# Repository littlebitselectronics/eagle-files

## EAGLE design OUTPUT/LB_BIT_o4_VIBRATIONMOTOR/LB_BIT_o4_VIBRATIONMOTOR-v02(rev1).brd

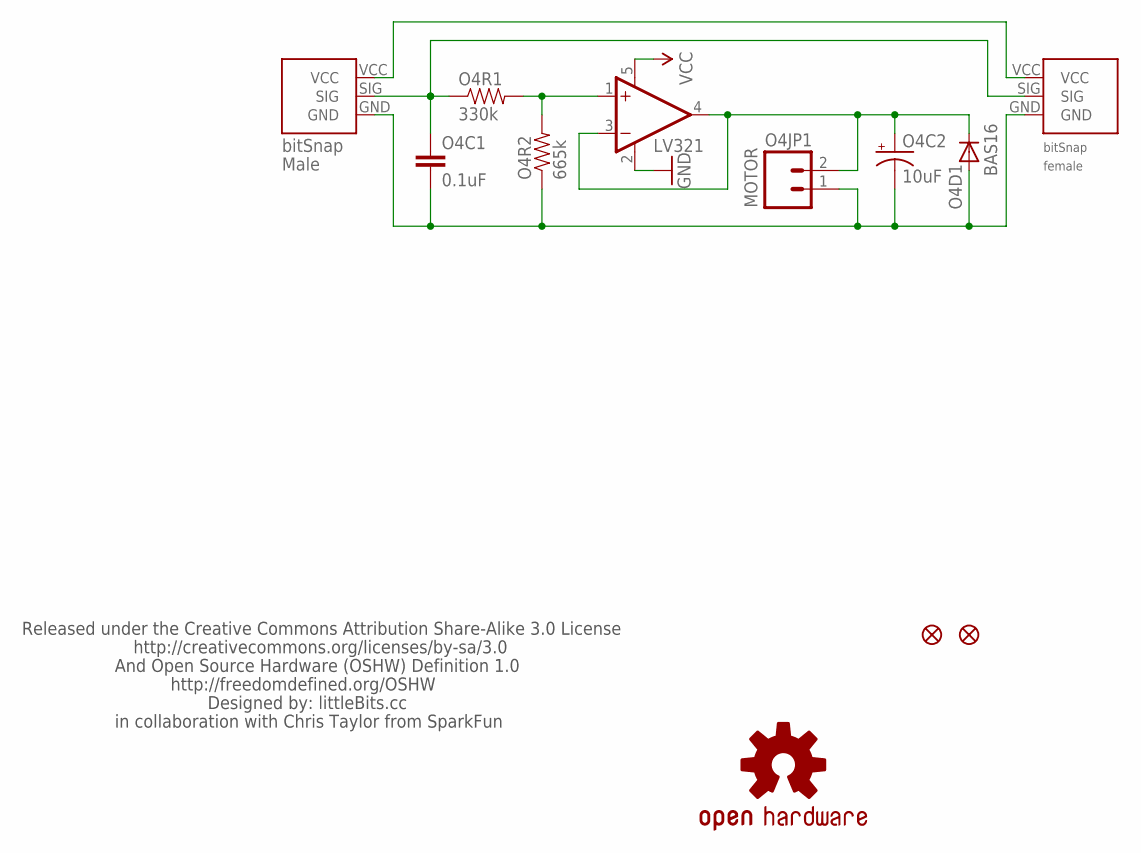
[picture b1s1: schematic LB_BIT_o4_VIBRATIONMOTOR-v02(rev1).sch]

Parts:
JP2, JP3: FIDUCIAL1X2.5; FIDUCIAL-1X2.5
O4BSF: BITSNAP_FEMALE
O4BSM: BITSNAP_MALE
O4C1: 0.1uF; 0603-CAP
O4C2: 10uF; EIA3216
O4D1: BAS16; SOT23-3
O4JP1: MOTOR; 1X02
O4R1: 330k; 0603-RES
O4R2: 665k; 0603-RES
O4U1: LV321; SC70
U$1: LB_CREDITS; OSHWCREDIT
U$5: OSHW-LOGOL; OSHW-LOGO-L

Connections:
GND: O4BSF.GND, O4BSM.GND, O4C1.2, O4C2.C (-), O4D1.1 (A), O4JP1.1, O4R2.1, O4U1.2 (V-)
unnamed: O4C2.A (+), O4D1.3 (C), O4JP1.2, O4U1.3 (-IN), O4U1.4 (OUT)
unnamed: O4R1.2, O4R2.2, O4U1.1 (+IN)
SIG: O4BSF.SIG, O4BSM.SIG, O4C1.1, O4R1.1
VCC: O4BSF.VCC, O4BSM.VCC, O4U1.5 (V+)

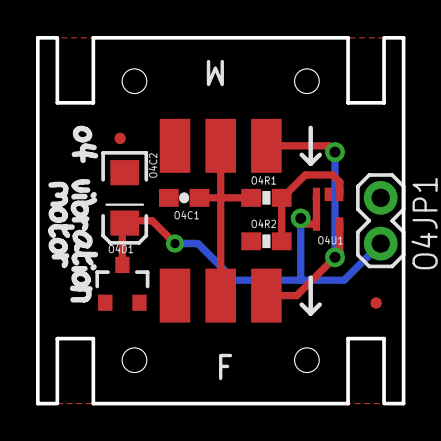
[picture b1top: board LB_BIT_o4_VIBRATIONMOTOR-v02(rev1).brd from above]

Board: 2 copper layers, 20.3 x 20.3 mm, 14 parts (0 on the bottom side), 5 nets.

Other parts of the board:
U$4: OSHW_FILLX150_NOTEXT

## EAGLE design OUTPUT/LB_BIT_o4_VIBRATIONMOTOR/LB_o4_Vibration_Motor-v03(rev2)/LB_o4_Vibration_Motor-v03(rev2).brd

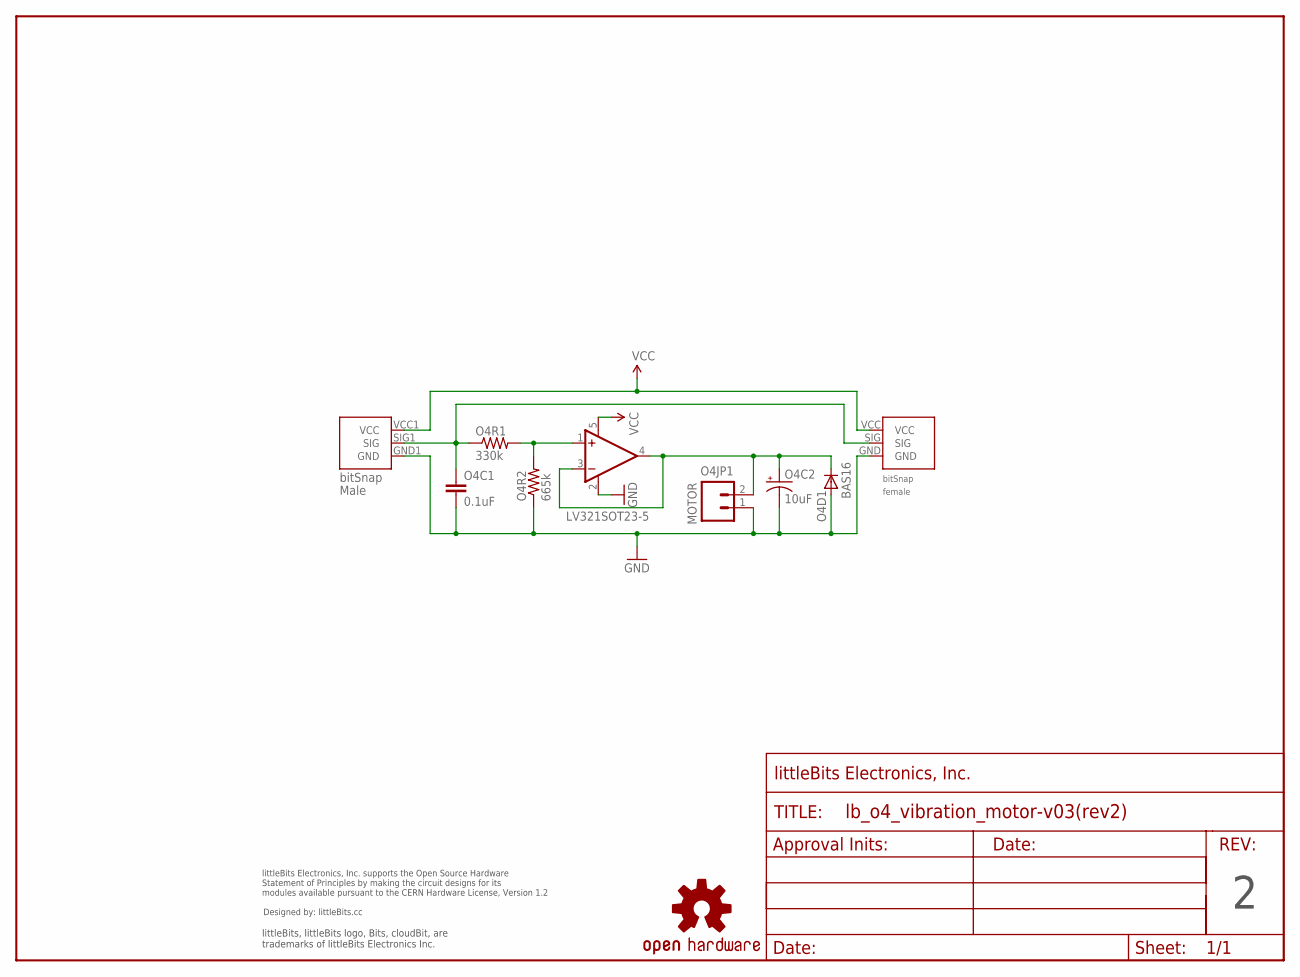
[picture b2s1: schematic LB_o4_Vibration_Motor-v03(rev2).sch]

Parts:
O4BSF1: BITSNAP_V03_FEMALE
O4BSM1: BITSNAP_V03_MALE
O4C1: 0.1uF; 0603-CAP
O4C2: 10uF; EIA3216
O4D1: BAS16; SOT23-3
O4JP1: MOTOR; JST-MICRO_2P
O4R1: 330k; 0603-RES
O4R2: 665k; 0603-RES
O4U1: LV321SOT23-5; SOT23-5
U$1: OSHWCREDIT
U$2: FRAME-LETTER-OHWOHW; FABDWG01-OHW
U$5: OSHW-LOGOL; OSHW-LOGO-L

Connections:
GND: O4BSF1.GND, O4BSM1.GND1 (GND), O4C1.2, O4C2.C (-), O4D1.1 (A), O4JP1.1, O4R2.1, O4U1.2 (V-)
unnamed: O4C2.A (+), O4D1.3 (C), O4JP1.2, O4U1.3 (-IN), O4U1.4 (OUT)
unnamed: O4R1.2, O4R2.2, O4U1.1 (+IN)
SIG: O4BSF1.SIG, O4BSM1.SIG1 (SIG), O4C1.1, O4R1.1
VCC: O4BSF1.VCC, O4BSM1.VCC1 (VCC), O4U1.5 (V+)

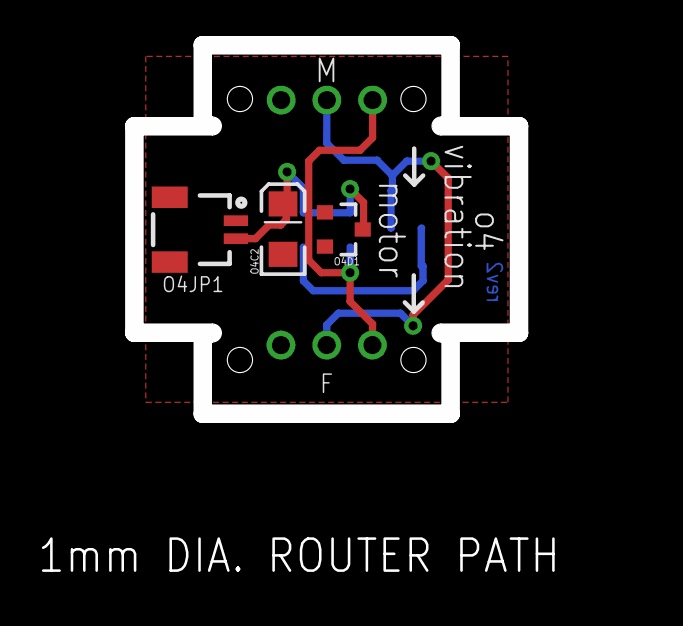
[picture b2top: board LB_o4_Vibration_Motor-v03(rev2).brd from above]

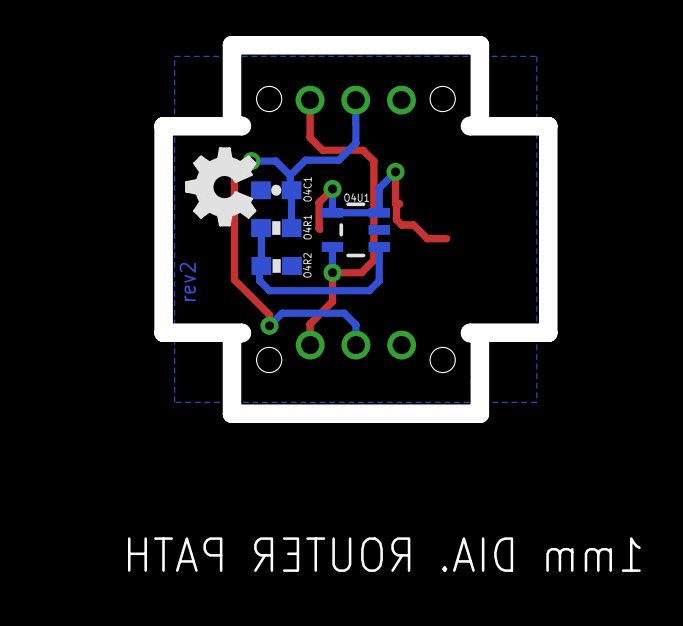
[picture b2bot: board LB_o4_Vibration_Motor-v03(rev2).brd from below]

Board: 2 copper layers, 21.4 x 20.5 mm, 13 parts (4 on the bottom side), 5 nets.

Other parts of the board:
U$4: OSHW_FILLX150_NOTEXT

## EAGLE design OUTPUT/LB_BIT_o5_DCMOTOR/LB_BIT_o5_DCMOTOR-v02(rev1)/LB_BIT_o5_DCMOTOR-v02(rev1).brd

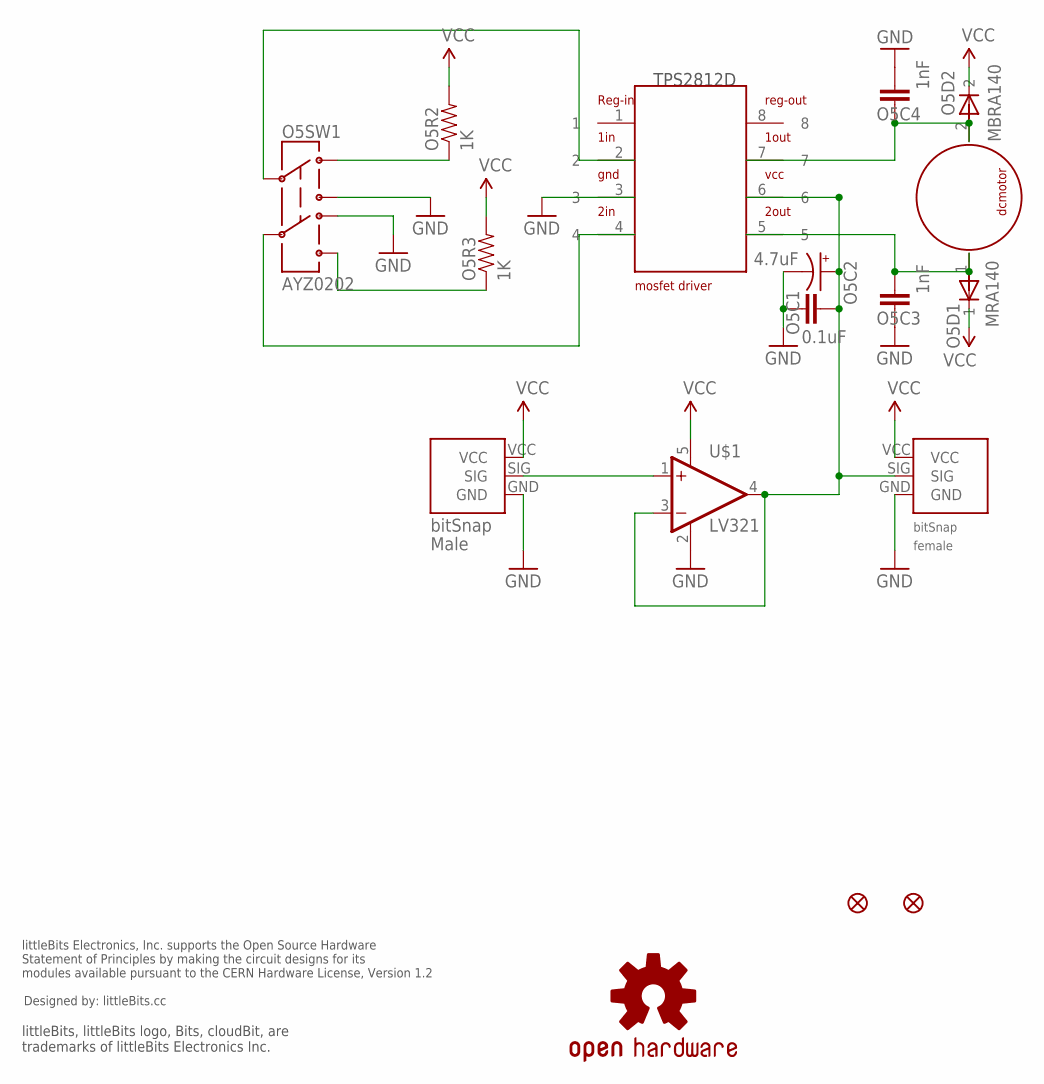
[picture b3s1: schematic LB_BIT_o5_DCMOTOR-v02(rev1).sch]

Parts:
JP1, JP2: FIDUCIAL1X2; FIDUCIAL-1X2
O5BSF: BITSNAP_FEMALE
O5BSM: BITSNAP_MALE
O5C1: 0.1uF; 0603-CAP
O5C2: 4.7uF; EIA3216
O5C3, O5C4: 1nF; 0603-CAP
O5D1: MRA140; SMA-DIODE
O5D2: MBRA140; SMA-DIODE
O5M1: DCMOTOR; MOTOR-DC
O5R2, O5R3: 1K; 0603-RES
O5SW1: AYZ0202
O5U1: TPS2812-SOIC8; TPS2812
U$1: LV321; SC70-5
U$4: OSHW-LOGOL; OSHW-LOGO-L
U$6: OSHWCREDIT

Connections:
GND: O5BSF.GND, O5BSM.GND, O5C1.1, O5C2.C (-), O5C3.1, O5C4.2, O5SW1.1 (3), O5SW1.6 (4), O5U1.3, U$1.2 (V-)
unnamed: O5BSM.SIG, U$1.1 (+IN)
unnamed: O5R2.1, O5SW1.3 (1)
unnamed: O5R3.1, O5SW1.4 (6)
unnamed: O5SW1.5, O5U1.4
unnamed: O5SW1.2, O5U1.2
unnamed: O5C4.1, O5D2.A, O5M1.2, O5U1.7
unnamed: O5C3.2, O5D1.A, O5M1.1, O5U1.5
SIG: O5BSF.SIG, O5C1.2, O5C2.A (+), O5U1.6, U$1.3 (-IN), U$1.4 (OUT)
VCC: O5BSF.VCC, O5BSM.VCC, O5D1.C, O5D2.C, O5R2.2, O5R3.2, U$1.5 (V+)

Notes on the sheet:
TPS2812D

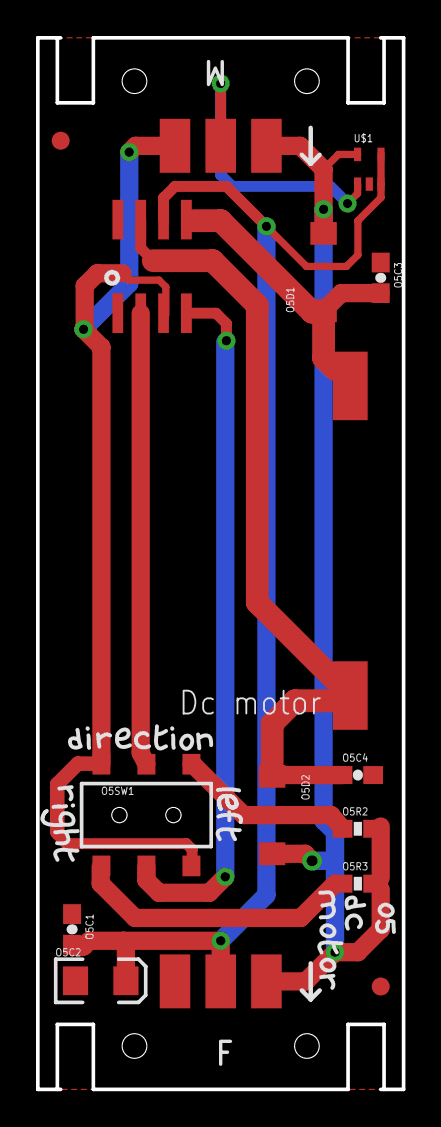
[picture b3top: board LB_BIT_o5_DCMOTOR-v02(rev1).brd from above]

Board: 2 copper layers, 20.3 x 58.4 mm, 47 parts (0 on the bottom side), 10 nets.

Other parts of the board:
U$2, U$38, U$40, U$49: O
U$3: 5
U$5, U$42: D
U$8: OSHW_FILLX150_NOTEXT
U$36, U$46: C
U$37: M
U$39, U$47, U$55, U$60: T
U$41, U$44, U$56: R
U$43, U$48, U$57: I
U$45, U$52, U$53: E
U$50: N
U$51: L
U$54: F
U$58: G
U$59: H

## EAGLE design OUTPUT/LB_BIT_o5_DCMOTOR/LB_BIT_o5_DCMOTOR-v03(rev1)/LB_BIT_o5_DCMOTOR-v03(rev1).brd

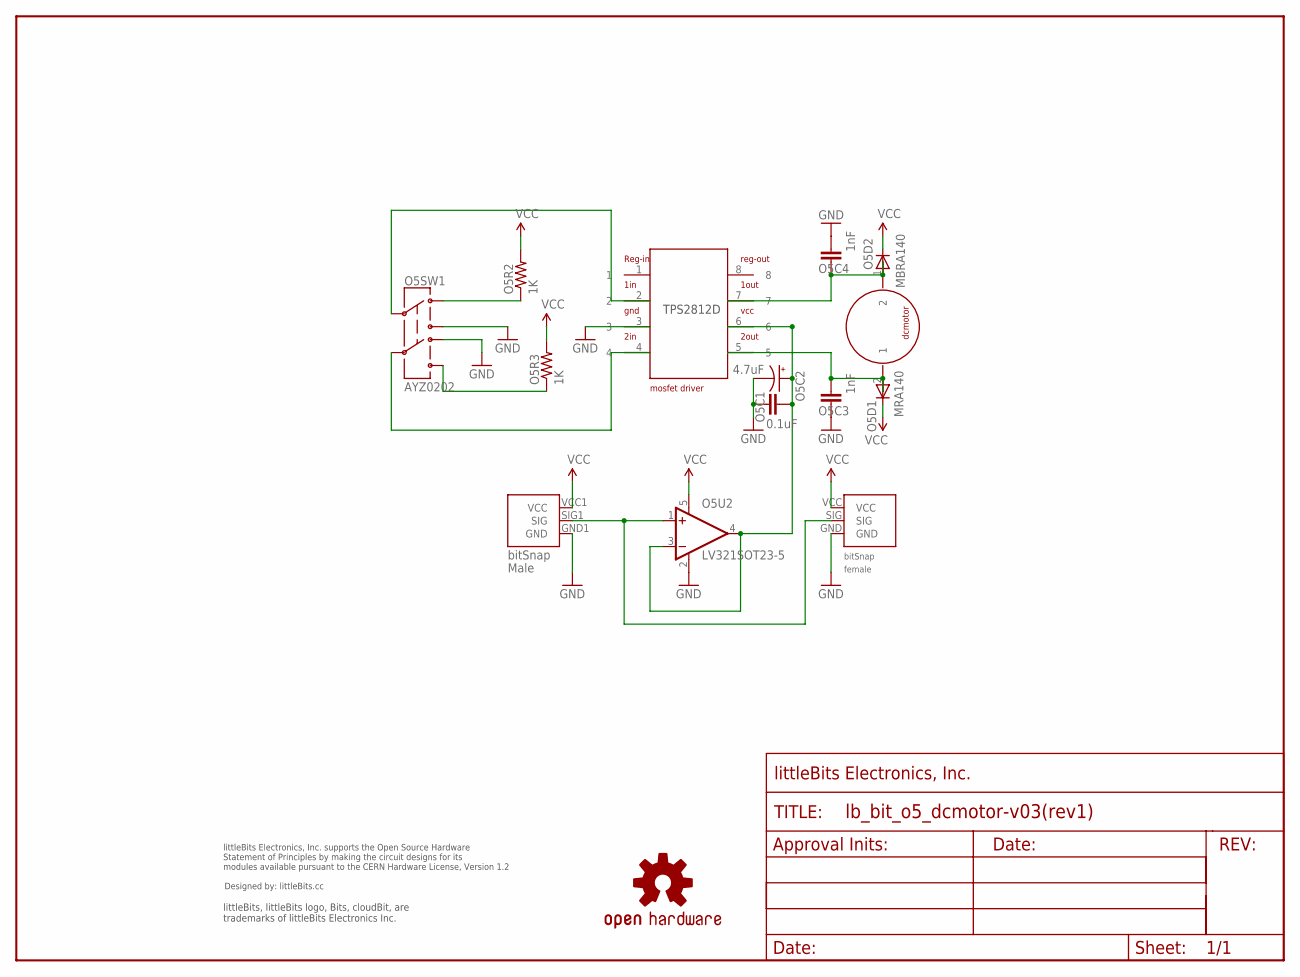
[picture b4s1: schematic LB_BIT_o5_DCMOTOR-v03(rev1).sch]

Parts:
O5BSF1: BITSNAP_V03_FEMALE
O5BSM1: BITSNAP_V03_MALE
O5C1: 0.1uF; 0603-CAP
O5C2: 4.7uF; EIA3216
O5C3, O5C4: 1nF; 0603-CAP
O5D1: MRA140; SMA-DIODE
O5D2: MBRA140; SMA-DIODE
O5M1: MOTOR-DC-GEARED; MOTOR-GEARED
O5R2, O5R3: 1K; 0603-RES
O5SW1: AYZ0202
O5U1: TPS2812-SOIC8; TPS2812
O5U2: LV321SOT23-5; SOT23-5
U$1: OSHWCREDIT
U$2: FRAME-LETTER-OHWOHW; FABDWG01-OHW
U$4: OSHW-LOGOL; OSHW-LOGO-L

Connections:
GND: O5BSF1.GND, O5BSM1.GND1 (GND), O5C1.1, O5C2.C (-), O5C3.1, O5C4.2, O5SW1.1 (3), O5SW1.6 (4), O5U1.3, O5U2.2 (V-)
unnamed: O5BSF1.SIG, O5BSM1.SIG1 (SIG), O5U2.1 (+IN)
unnamed: O5R2.1, O5SW1.3 (1)
unnamed: O5R3.1, O5SW1.4 (6)
unnamed: O5SW1.5, O5U1.4
unnamed: O5SW1.2, O5U1.2
unnamed: O5C4.1, O5D2.A, O5M1.1 (2), O5U1.7
unnamed: O5C3.2, O5D1.A, O5M1.2 (1), O5U1.5
SIG: O5C1.2, O5C2.A (+), O5U1.6, O5U2.3 (-IN), O5U2.4 (OUT)
VCC: O5BSF1.VCC, O5BSM1.VCC1 (VCC), O5D1.C, O5D2.C, O5R2.2, O5R3.2, O5U2.5 (V+)

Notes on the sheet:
TPS2812D

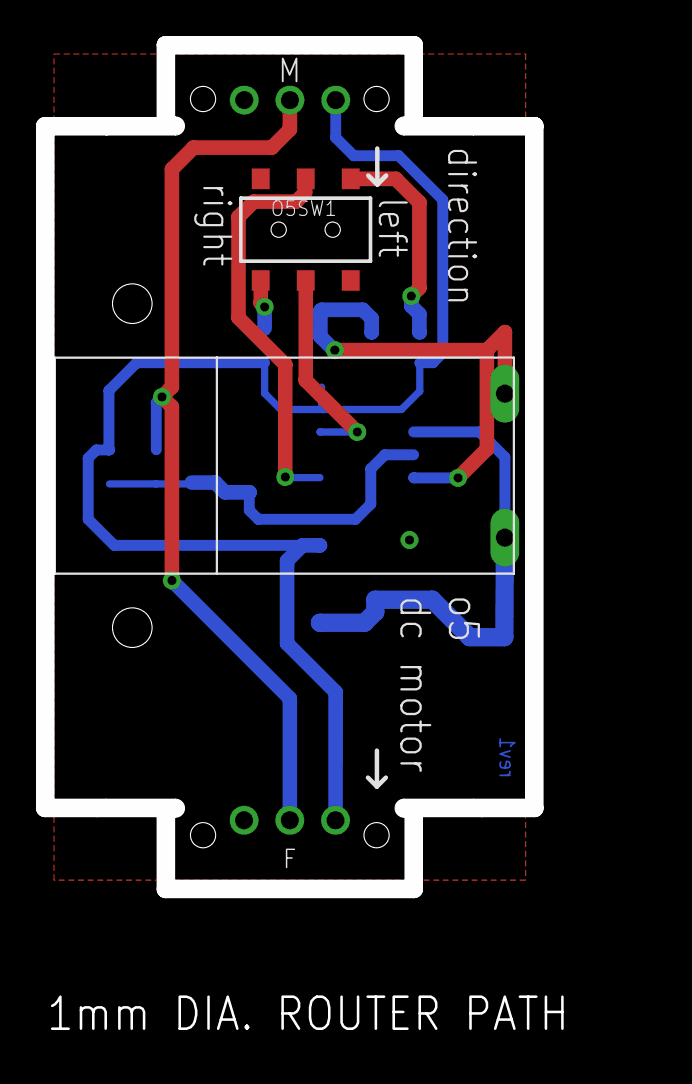
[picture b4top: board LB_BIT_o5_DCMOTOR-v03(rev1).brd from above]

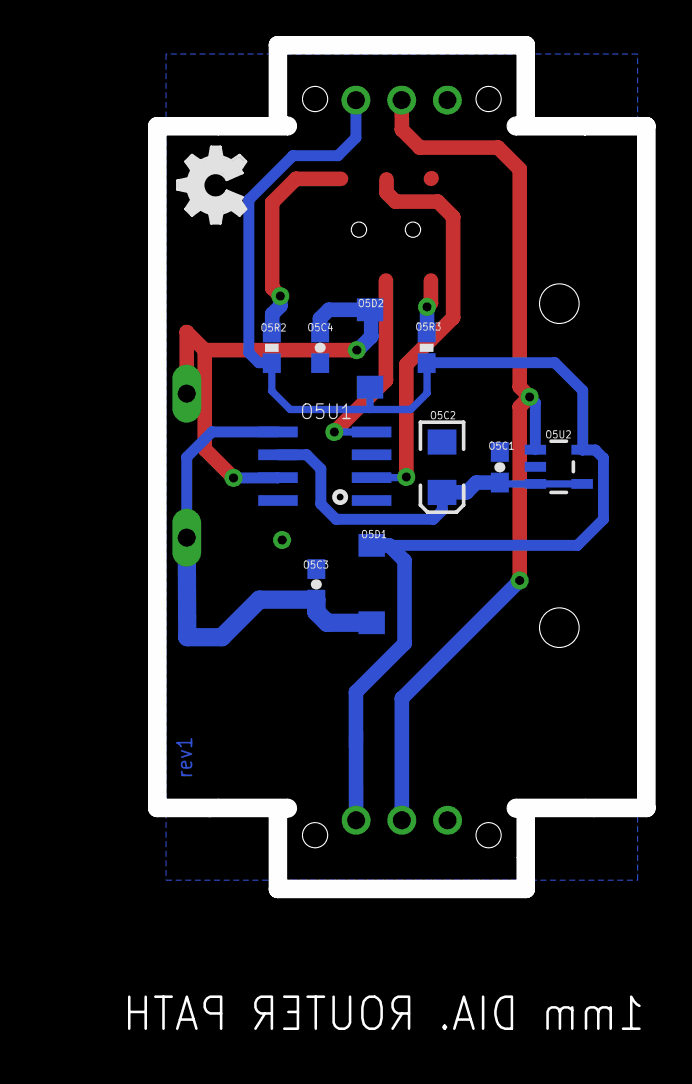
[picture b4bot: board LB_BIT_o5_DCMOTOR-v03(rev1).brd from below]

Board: 2 copper layers, 27.2 x 46.9 mm, 18 parts (10 on the bottom side), 10 nets.

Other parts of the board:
U$8: OSHW_FILLX150_NOTEXT

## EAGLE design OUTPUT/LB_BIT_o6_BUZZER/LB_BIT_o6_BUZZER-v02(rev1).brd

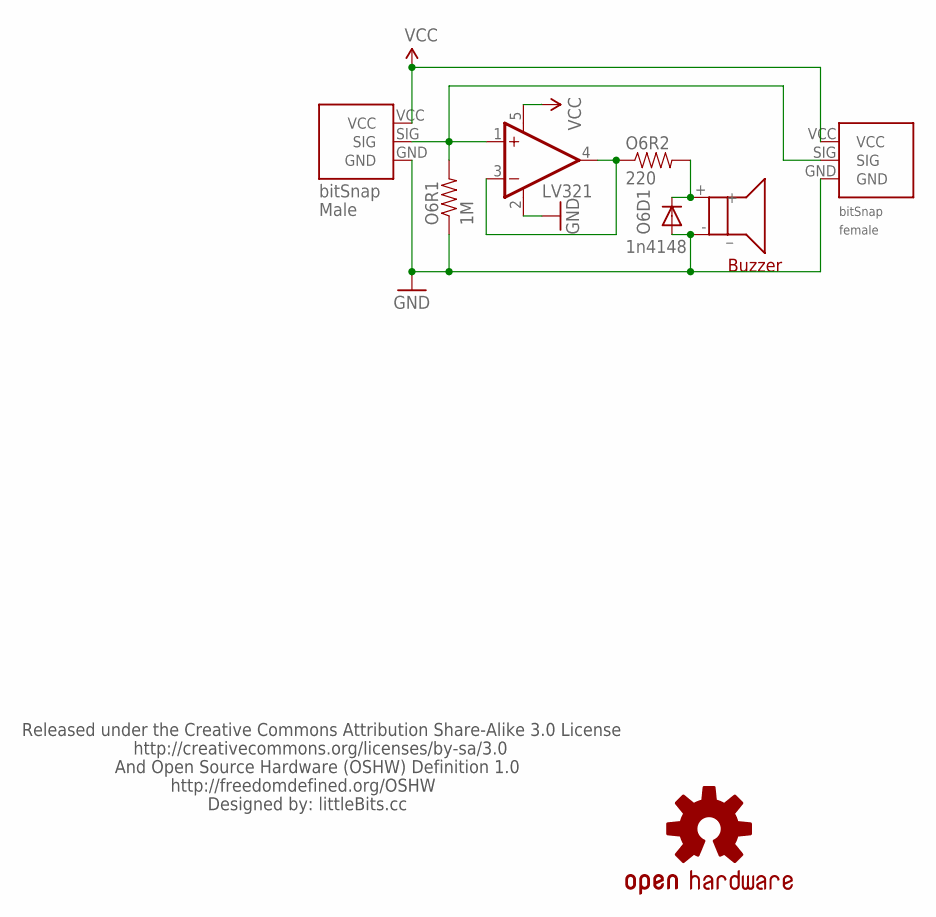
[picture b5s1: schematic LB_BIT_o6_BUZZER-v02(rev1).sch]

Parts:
O6BSF: BITSNAP_FEMALE
O6BSM: BITSNAP_MALE
O6D1: 1n4148; SOD-323
O6R1: 1M; 0603-RES
O6R2: 220; 0603-RES
O6U1: BUZZER-JSH2317AT
U$2: LV321; SC70
U$15: LB_CREDITS_V2
U$16: OSHW-LOGOL; OSHW-LOGO-L

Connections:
GND: O6BSF.GND, O6BSM.GND, O6D1.2 (A), O6R1.1, O6U1.- (_), U$2.2 (V-)
unnamed: O6D1.1 (C), O6R2.2, O6U1.+
unnamed: O6BSF.SIG, O6BSM.SIG, O6R1.2, U$2.1 (+IN)
unnamed: O6R2.1, U$2.3 (-IN), U$2.4 (OUT)
VCC: O6BSF.VCC, O6BSM.VCC, U$2.5 (V+)

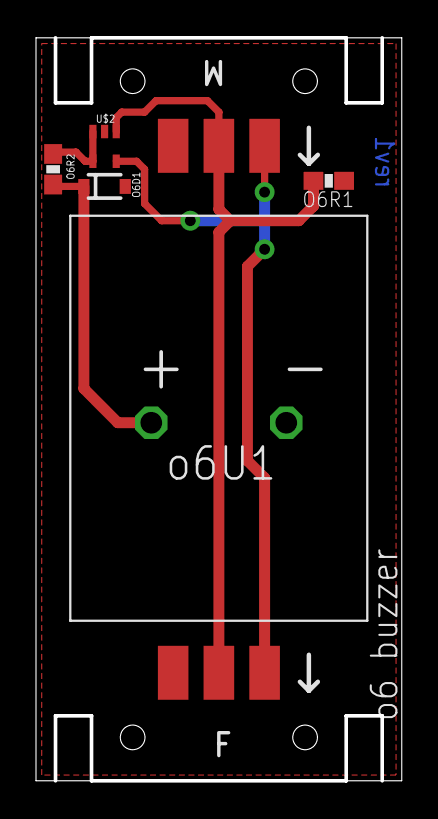
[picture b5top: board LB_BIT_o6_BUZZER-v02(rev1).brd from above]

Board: 2 copper layers, 20.3 x 41.3 mm, 10 parts (0 on the bottom side), 5 nets.

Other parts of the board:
U$7: OSHW_FILLX150_NOTEXT

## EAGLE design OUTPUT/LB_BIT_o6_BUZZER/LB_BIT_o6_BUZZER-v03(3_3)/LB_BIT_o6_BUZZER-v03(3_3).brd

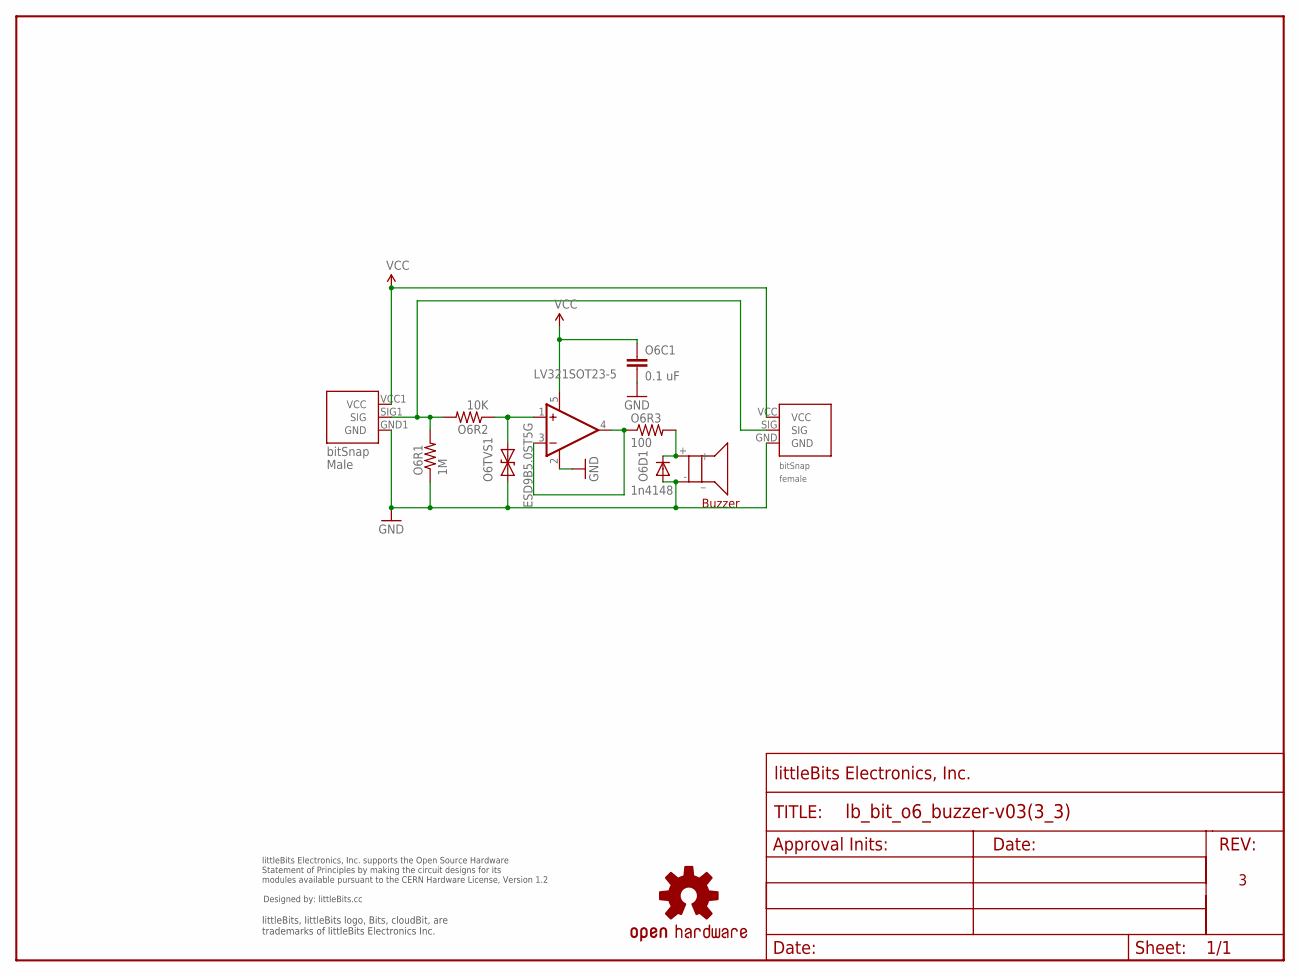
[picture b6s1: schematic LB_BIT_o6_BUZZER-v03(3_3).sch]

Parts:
O6BSF1: BITSNAP_V03_FEMALE
O6BSM1: BITSNAP_V03_MALE
O6C1: 0.1 uF; CAP-0603
O6D1: 1n4148; SOD-323
O6R1: 1M; RES-0603
O6R2: 10K; RES-0603
O6R3: 100; RES-0603
O6TVS1: ESD9B5.0ST5G; SOD-923
O6U1: LV321SOT23-5; SOT23-5
O6U2: BUZZER-JSH2317AT
U$1: FRAME-LETTER-OHWOHW; FABDWG01-OHW
U$2: OSHWCREDIT
U$16: OSHW-LOGOL; OSHW-LOGO-L

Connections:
GND: O6BSF1.GND, O6BSM1.GND1 (GND), O6C1.2, O6D1.2 (A), O6R1.1, O6TVS1.1 (A), O6U1.2 (V-), O6U2.- (_)
unnamed: O6D1.1 (C), O6R3.2, O6U2.+
unnamed: O6R2.1, O6TVS1.2 (C), O6U1.1 (+IN)
unnamed: O6BSF1.SIG, O6BSM1.SIG1 (SIG), O6R1.2, O6R2.2
unnamed: O6R3.1, O6U1.3 (-IN), O6U1.4 (OUT)
VCC: O6BSF1.VCC, O6BSM1.VCC1 (VCC), O6C1.1, O6U1.5 (V+)

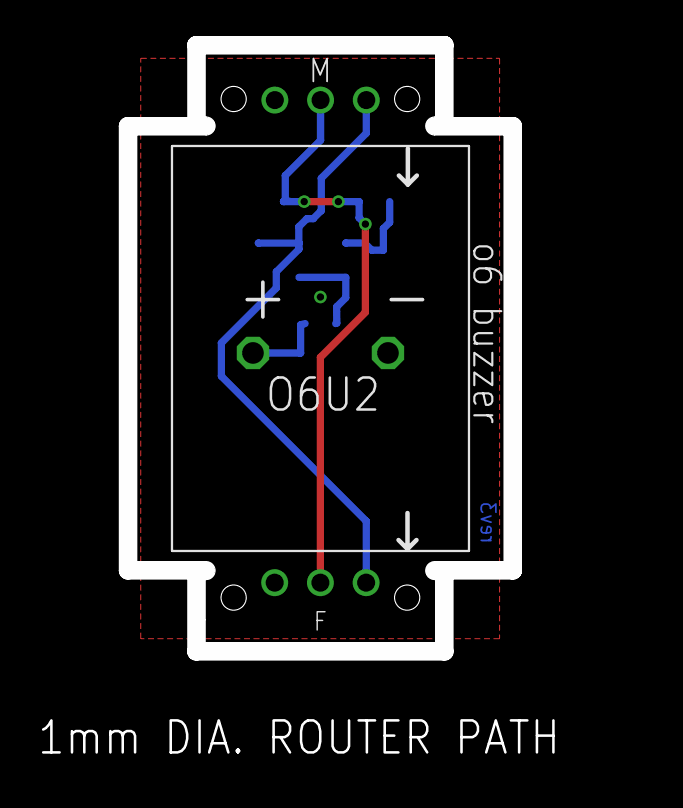
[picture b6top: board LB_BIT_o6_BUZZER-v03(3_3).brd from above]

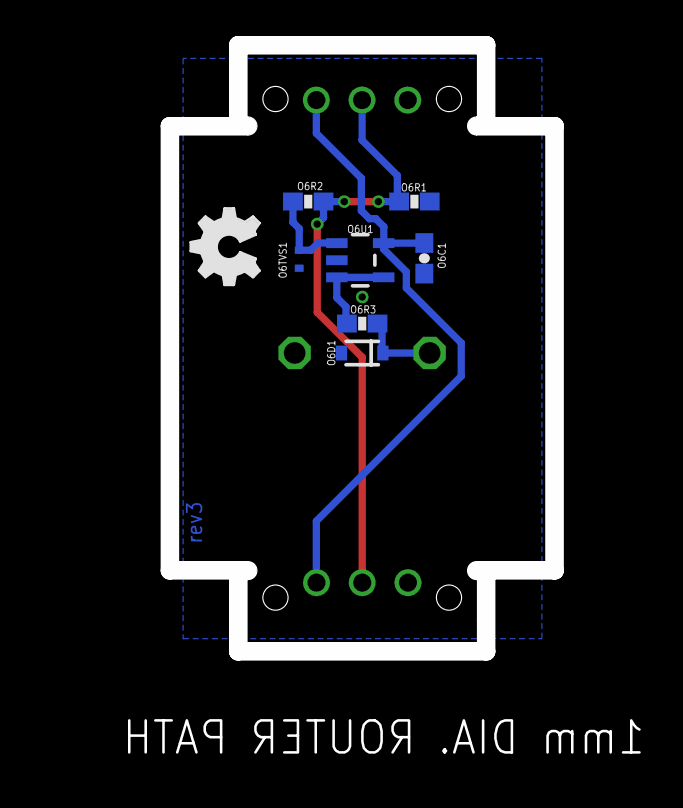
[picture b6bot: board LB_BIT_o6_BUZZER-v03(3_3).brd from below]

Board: 2 copper layers, 21.4 x 33.7 mm, 14 parts (7 on the bottom side), 6 nets.

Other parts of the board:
U$7: OSHW_FILLX150_NOTEXT

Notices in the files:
parts and their libraries:
LITTLEBITS: Released under the Creative Commons Attribution Share-Alike 3.0 License
LITTLEBITS: http://creativecommons.org/license/by-sa/3.0
LITTLEBITS: http://creativecommons.org/licenses/by-sa/3.0
LITTLEBITS: modules available pursuant to the CERN Hardware License,
Version 1.2
